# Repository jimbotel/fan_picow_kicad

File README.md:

# fan_picow_kicad
 KiCad6 project for my raspberry pi picow fan controller

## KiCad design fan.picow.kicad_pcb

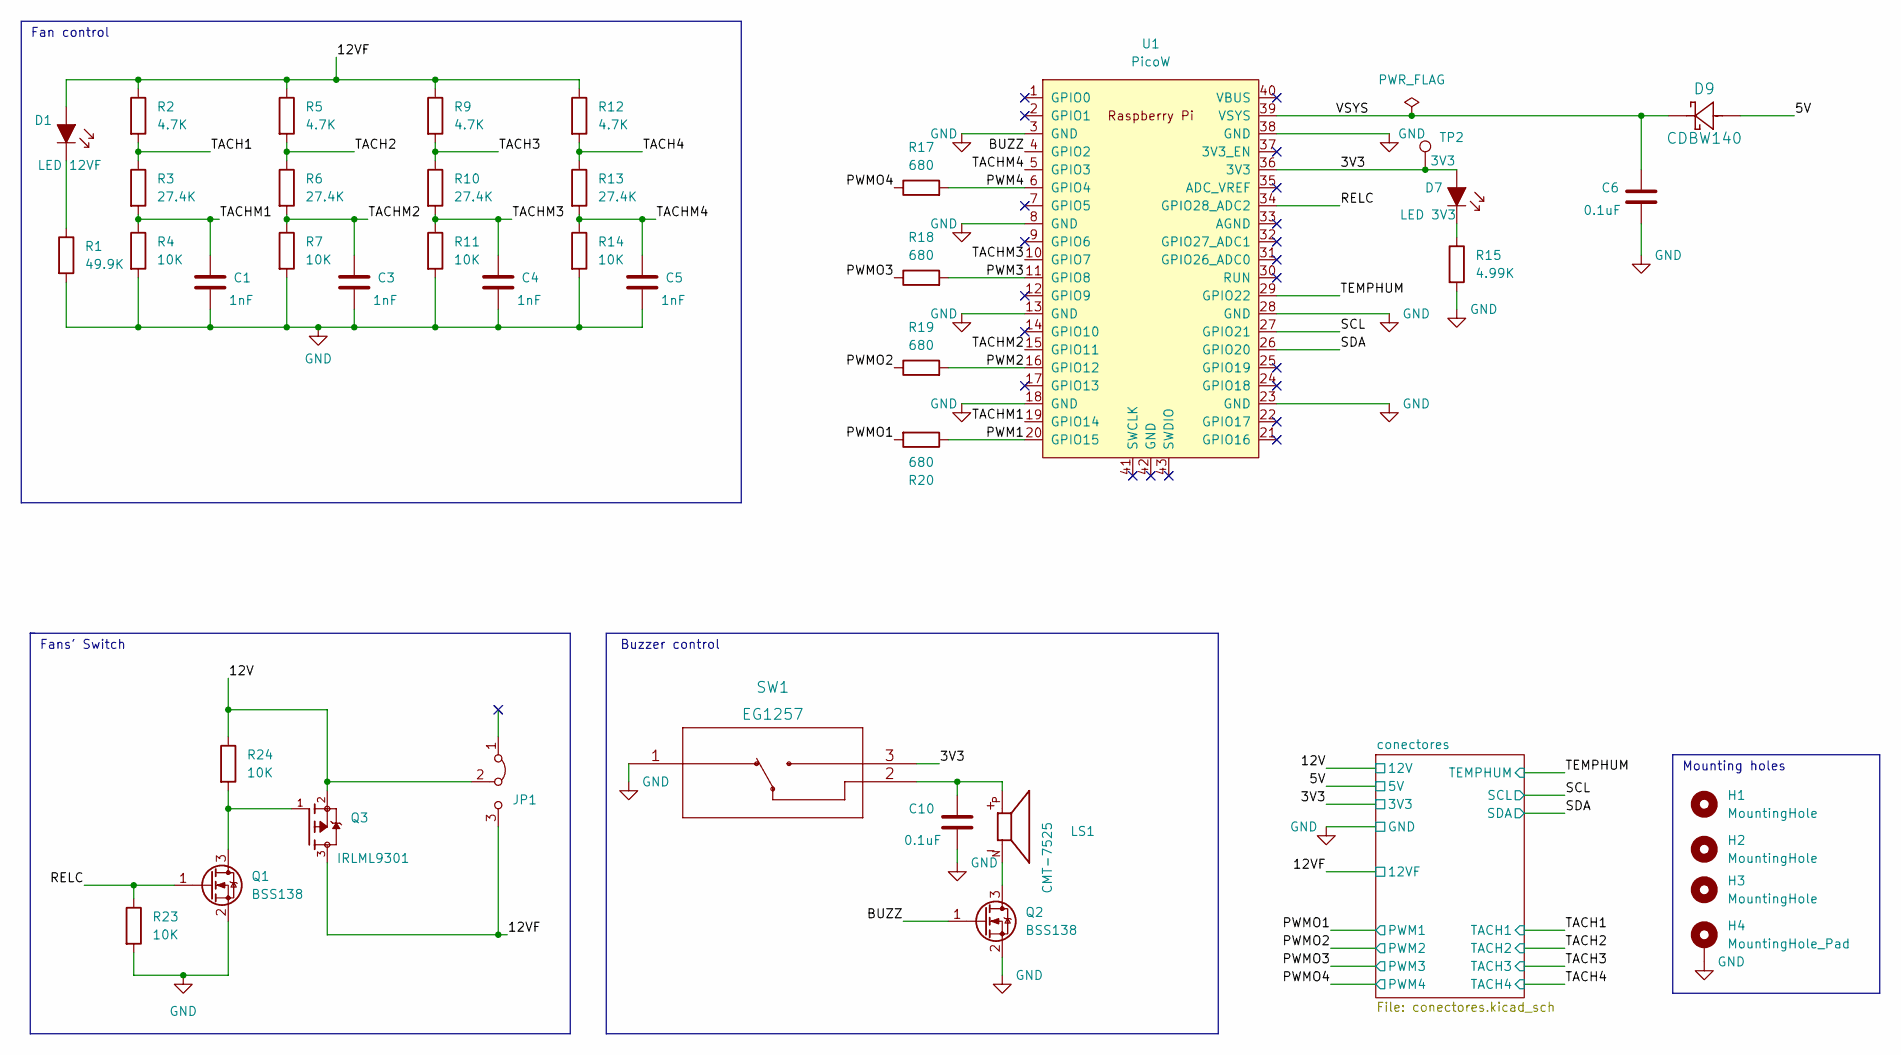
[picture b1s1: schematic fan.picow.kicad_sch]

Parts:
C1, C3, C4, C5: 1nF; C_1206_3216Metric_Pad1.33x1.80mm_HandSolder
C6, C10: 0.1uF; C_1206_3216Metric_Pad1.33x1.80mm_HandSolder
D1: LED 12VF; 0805; MPN LG R971-KN-1; Digi-Key_PN 475-1410-1-ND
D7: LED 3V3; 0805; MPN LG R971-KN-1; Digi-Key_PN 475-1410-1-ND
D9: CDBW140; D_SOD-123F
H1, H2, H3: MountingHole; MountingHole_3.2mm_M3
H4: MountingHole_Pad; MountingHole_3.2mm_M3_Pad_Via
JP1: Jumper_3_Bridged12; PinHeader_1x03_P2.54mm_Vertical
LS1: CMT-7525; XDCR_CMT-7525-80-SMT-TR; PARTREV N/A
Q1, Q2: BSS138; SOT-23
Q3: IRLML9301; IRLML9301TRPBF.SOT95P237X112-3N
R1: 49.9K; R_1206_3216Metric_Pad1.30x1.75mm_HandSolder
R2, R5, R9, R12: 4.7K; R_1206_3216Metric_Pad1.30x1.75mm_HandSolder
R3, R6, R10, R13: 27.4K; R_1206_3216Metric_Pad1.30x1.75mm_HandSolder
R4, R7, R11, R14, R23, R24: 10K; R_1206_3216Metric_Pad1.30x1.75mm_HandSolder
R15: 4.99K; R_1206_3216Metric_Pad1.30x1.75mm_HandSolder
R17, R18, R19, R20: 680; R_1206_3216Metric_Pad1.30x1.75mm_HandSolder
SW1: EG1257
TP2: 3V3; TestPoint_Pad_D1.5mm
U1: PicoW; RPi_PicoW_SMD_TH

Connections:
/3V3: D7.1, SW1.3, TP2.1, U1.36 (3V3); also elsewhere on the board
/5V: D9.2; also elsewhere on the board
/12V: JP1.2 (C), Q3.2, R24.1; also elsewhere on the board
/12VF: D1.1, JP1.3 (B), Q3.3, R2.1, R5.1, R9.1, R12.1; also elsewhere on the board
/BUZZ: Q2.1 (G), U1.4 (GPIO2)
/PWM1: R20.1, U1.20 (GPIO15)
/PWM2: R19.2, U1.16 (GPIO12)
/PWM3: R18.2, U1.11 (GPIO8)
/PWM4: R17.2, U1.6 (GPIO4)
/PWMO1: R20.2; also elsewhere on the board
/PWMO2: R19.1; also elsewhere on the board
/PWMO3: R18.1; also elsewhere on the board
/PWMO4: R17.1; also elsewhere on the board
/RELC: Q1.1 (G), R23.1, U1.34 (GPIO28_ADC2)
/SCL: U1.27 (GPIO21); also elsewhere on the board
/SDA: U1.26 (GPIO20); also elsewhere on the board
/TACH1: R2.2, R3.1; also elsewhere on the board
/TACH2: R5.2, R6.1; also elsewhere on the board
/TACH3: R9.2, R10.1; also elsewhere on the board
/TACH4: R12.2, R13.1; also elsewhere on the board
/TACHM1: C1.1, R3.2, R4.1, U1.19 (GPIO14)
/TACHM2: C3.1, R6.2, R7.1, U1.15 (GPIO11)
/TACHM3: C4.1, R10.2, R11.1, U1.10 (GPIO7)
/TACHM4: C5.1, R13.2, R14.1, U1.5 (GPIO3); also elsewhere on the board
/TEMPHUM: U1.29 (GPIO22); also elsewhere on the board
/VSYS: C6.1, D9.1, U1.39 (VSYS)
GND: C1.2, C3.2, C4.2, C5.2, C6.2, C10.2, H4.1, Q1.2 (S), Q2.2 (S), R1.2, R4.2, R7.2, R11.2, R14.2, R15.2, R23.2, SW1.1, U1.3 (GND), U1.8 (GND), U1.13 (GND), U1.18 (GND), U1.23 (GND), U1.28 (GND), U1.38 (GND); also elsewhere on the board
unnamed: C10.1, LS1.P, SW1.2
unnamed: D1.2, R1.1
unnamed: D7.2, R15.1
unnamed: LS1.N, Q2.3 (D)
unnamed: Q1.3 (D), Q3.1, R24.2

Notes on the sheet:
Fans' Switch
Mounting holes
Fan control
Buzzer control

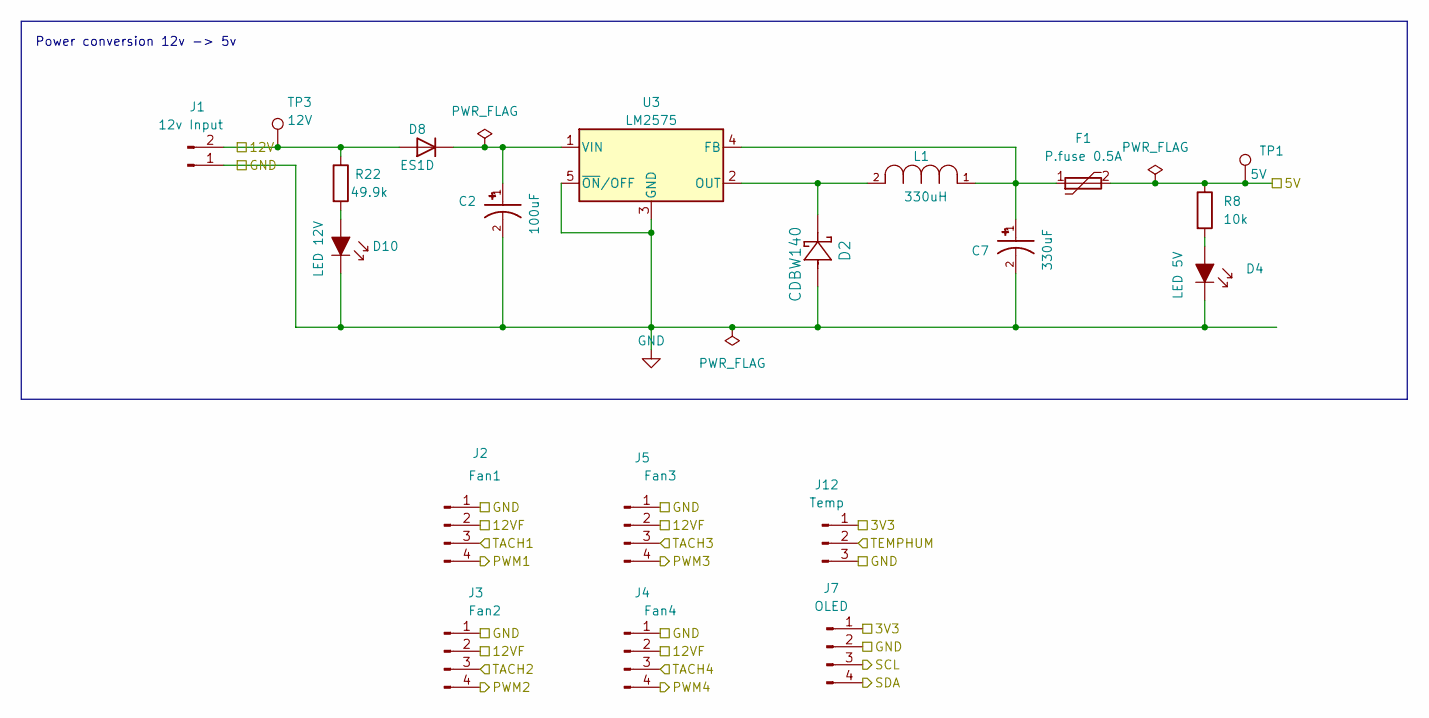
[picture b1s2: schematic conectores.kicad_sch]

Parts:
C2: 100uF; CAP_EEEHA1V101XP; PARTREV 10-Oct-19
C7: 330uF; CAP_EEEFT1V331AP; PARTREV 10-Oct-19
D2: CDBW140; D_SOD-123F
D4: LED 5V; 0805; MPN LG R971-KN-1; Digi-Key_PN 475-1410-1-ND
D8: ES1D; D_1206_3216Metric_Pad1.42x1.75mm_HandSolder
D10: LED 12V; 0805; MPN LG R971-KN-1; Digi-Key_PN 475-1410-1-ND
F1: P.fuse 0.5A; Fuse_1206_3216Metric_Pad1.42x1.75mm_HandSolder
J1: 12v Input; PinHeader_1x02_P2.54mm_Vertical
J2: Fan1; FanPinHeader_1x04_P2.54mm_Vertical
J3: Fan2; FanPinHeader_1x04_P2.54mm_Vertical
J4: Fan4; FanPinHeader_1x04_P2.54mm_Vertical
J5: Fan3; FanPinHeader_1x04_P2.54mm_Vertical
J7: OLED; PinHeader_1x04_P2.54mm_Horizontal
J12: Temp; PinHeader_1x03_P2.54mm_Horizontal
L1: 330uH; DR127-331_INDM125125X800N; TOLERANCE ±20%; MPN DR127-331-R
R8: 10k; R_1206_3216Metric_Pad1.30x1.75mm_HandSolder
R22: 49.9k; R_1206_3216Metric_Pad1.30x1.75mm_HandSolder
TP1: 5V; TestPoint_Pad_D1.5mm
TP3: 12V; TestPoint_Pad_D1.5mm
U3: LM2575; TO-263-5_TabPin3

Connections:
/3V3: J7.1, J12.1; also elsewhere on the board
/5V: F1.2, R8.1, TP1.1; also elsewhere on the board
/12V: D8.2 (A), J1.2, R22.1, TP3.1; also elsewhere on the board
/12VF: J2.2, J3.2, J4.2, J5.2; also elsewhere on the board
/PWMO1: J2.4; also elsewhere on the board
/PWMO2: J3.4; also elsewhere on the board
/PWMO3: J5.4; also elsewhere on the board
/PWMO4: J4.4; also elsewhere on the board
/SCL: J7.3; also elsewhere on the board
/SDA: J7.4; also elsewhere on the board
/TACH1: J2.3; also elsewhere on the board
/TACH2: J3.3; also elsewhere on the board
/TACH3: J5.3; also elsewhere on the board
/TACH4: J4.3; also elsewhere on the board
/TEMPHUM: J12.2; also elsewhere on the board
GND: C2.2, C7.2, D2.2, D4.2, D10.2, J1.1, J2.1, J3.1, J4.1, J5.1, J7.2, J12.3, U3.3 (GND), U3.5 (~ON/OFF); also elsewhere on the board
unnamed: C2.1, D8.1 (K), U3.1 (VIN)
unnamed: C7.1, F1.1, L1.1, U3.4 (FB)
unnamed: D2.1, L1.2, U3.2 (OUT)
unnamed: D4.1, R8.2
unnamed: D10.1, R22.2

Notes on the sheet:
Power conversion 12v -> 5v

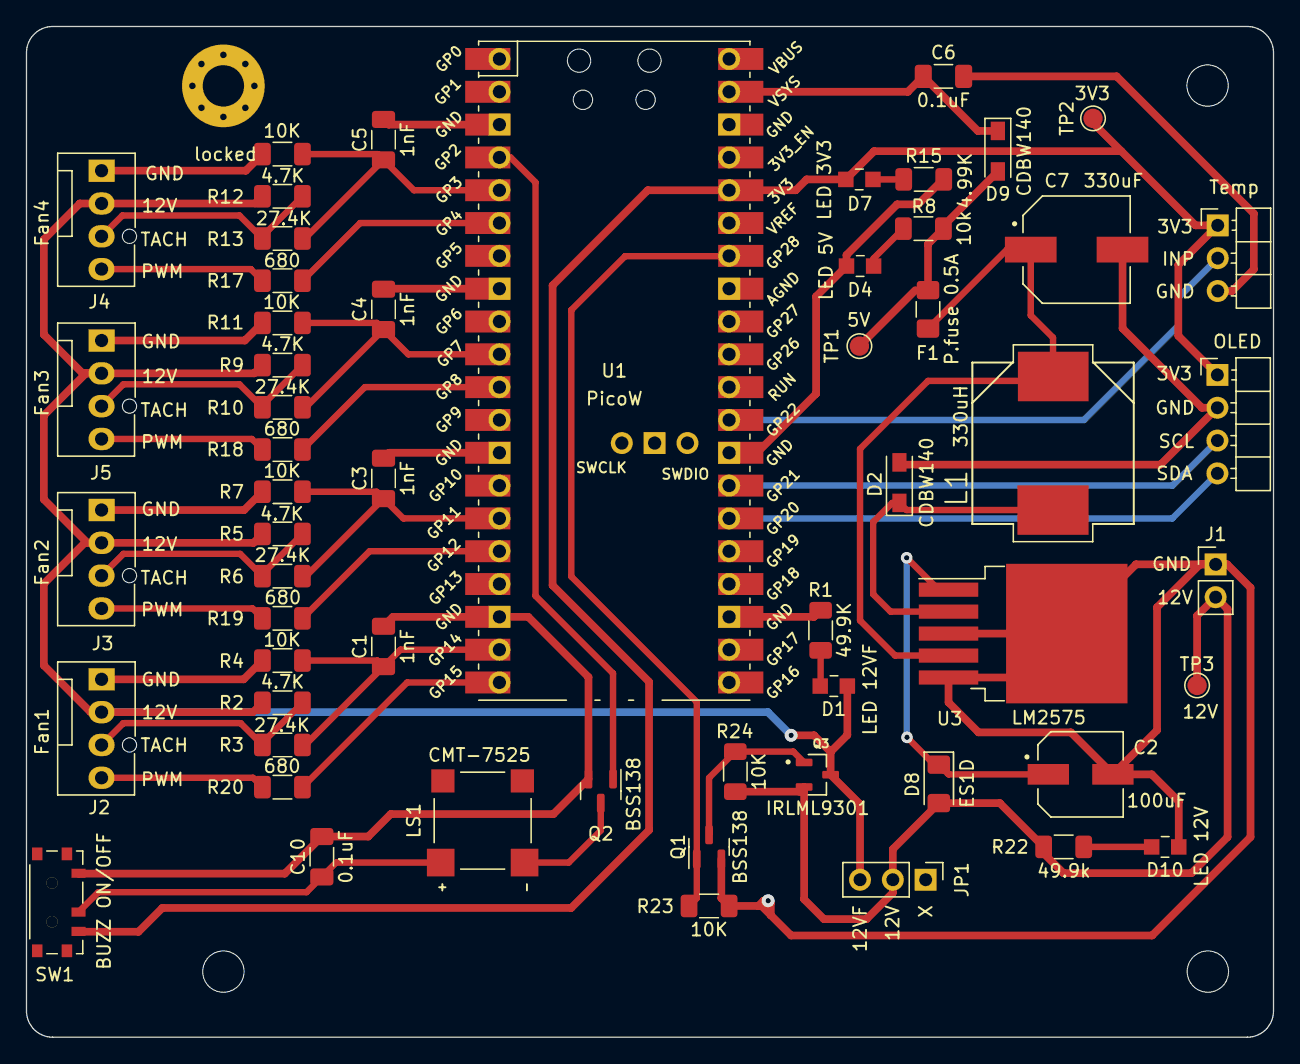
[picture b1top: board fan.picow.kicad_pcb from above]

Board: 2 copper layers, 96.5 x 78.2 mm, 61 parts (0 on the bottom side), 37 nets.

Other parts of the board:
locked: 10K; R_1206_3216Metric_Pad1.30x1.75mm_HandSolder

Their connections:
/TACHM4: locked.1; also elsewhere on the board
GND: locked.2; also elsewhere on the board

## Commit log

2023-01-20 version 2
    Functions added to the board (previously outside):
    - 12v to 5v conversion
    - Buzzer
    Footprints modified to the ones purchased
2023-01-20 Clean up ignored files
2023-01-20 pop stashed changes
2023-01-20 add Gerber dir to .gitignore
2023-01-20 Update .gitattributes
    Ignore PCB files during merge
2023-01-20 remove a comment
2023-01-20 add text box
2023-01-20 cleanup all tracks and vias
2023-01-20 minor text changes
2023-01-20 first autorouting test
2023-01-20 added *.rules to .gitignore
2023-01-20 add GNDFAN net to Power netclass
2023-01-29 add drive high-side switch
2023-04-02 edit some footprints to give more room to the pads
2023-04-03 resize pcb to match 100mm length
2023-04-04 back to rectangle shape
    Move switch to the left
    Move 12vf led to the bottom
    Remove vias -redo part of the layout
2023-04-04 synch sch and pcb
2023-04-05 Most SMD 1206 now
    Also increase track size to 0.5 for Default subnet
    And replace text so everything is more visible
2023-04-06 move buzz switch to the border
    also:
    - Redo GND connections around LM2575
    - Move some texts elements to make it neater
2023-04-06 round zone at the corners
2023-04-23 minor changes
    - Change L/C values 300 -> 330
    - Change footprint association: 12v pinheader is now vertical
    - Change 3D models for capacitors (replaced due to lack of stock)
    - Also changed some references to make it more neat
    - Add also a square around the fan switch area in the schematic
2023-04-24 add 3d models
    old pcb, just update 3d models
2023-04-24 change 3D model for capacitors

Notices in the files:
parts and their libraries:
Copyright 2021 Accelerated Designs. All rights reserved.
